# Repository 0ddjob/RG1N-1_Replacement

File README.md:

# RG1N-1_Replacement
Replacement board designs for the Soviet-era РГ1Н-1 connector

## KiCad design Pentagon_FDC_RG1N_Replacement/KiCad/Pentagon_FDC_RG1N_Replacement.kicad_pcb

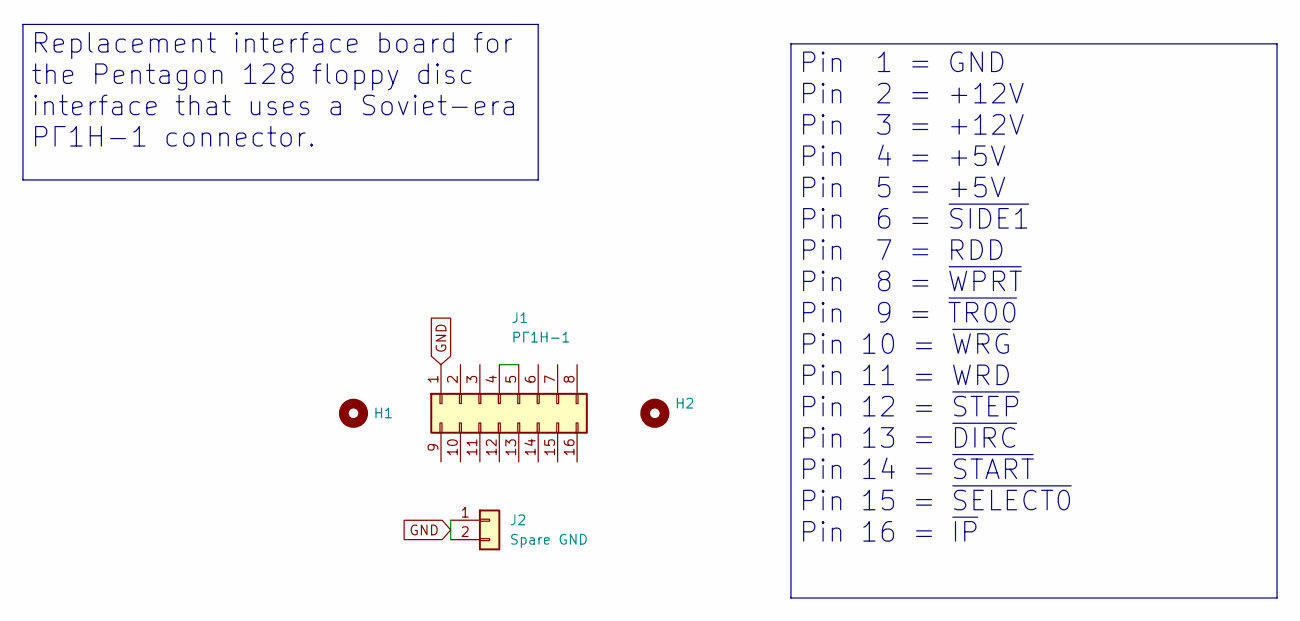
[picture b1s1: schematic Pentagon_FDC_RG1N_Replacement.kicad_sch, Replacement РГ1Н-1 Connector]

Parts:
H1, H2: MountingHole; MountingHole_3.2mm_M3
J1: РГ1Н-1; PinHeader_2x08_P2.54mm_Vertical
J2: Spare GND; PinHeader_1x02_P2.54mm_Vertical

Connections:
GND: J1.1, J2.1, J2.2
unnamed: J1.4, J1.5

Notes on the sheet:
Replacement interface board for the Pentagon 128 floppy disc interface that uses a Soviet-era РГ1Н-1 connector.
Pin 1 = GND Pin 2 = +12V Pin 3 = +12V Pin 4 = +5V Pin 5 = +5V Pin 6 = ~{SIDE1} Pin 7 = RDD Pin 8 = ~{WPRT} Pin 9 = ~{TR00} Pin 10 = ~{WRG} Pin 11 = WRD Pin 12 = ~{STEP} Pin 13 = ~{DIRC} Pin 14 = ~{START} Pin 15 = ~{SELECT0} Pin 16 = ~{IP}

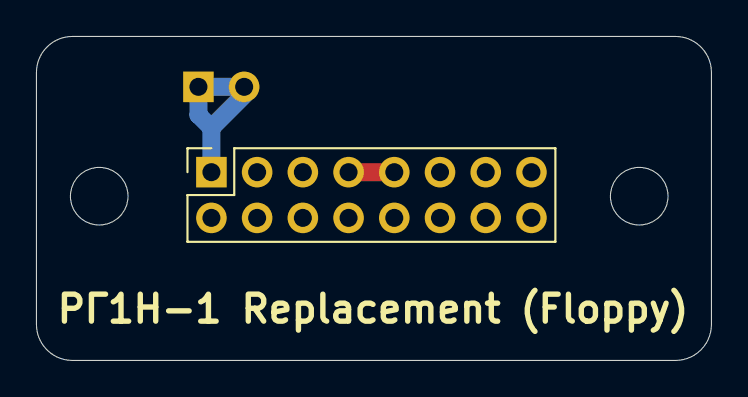
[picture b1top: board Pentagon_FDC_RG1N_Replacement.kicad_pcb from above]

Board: 2 copper layers, 37.5 x 18.0 mm, 4 parts (1 on the bottom side), 2 nets.

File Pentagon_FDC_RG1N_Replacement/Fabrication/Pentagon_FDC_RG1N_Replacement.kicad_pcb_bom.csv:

Designator,Quantity,Value,Footprint,Package,MPN,DNP,Mount_Type,Description
J1,1,РГ1Н-1,PinHeader_2x08_P2.54mm_Vertical,,,,tht,"Generic connector, double row, 02x08, top/bottom pin numbering scheme (row 1: 1...pins_per_row, row2: pins_per_row+1 ... num_pins), script generated (kicad-library-utils/schlib/autogen/connector/)"
J2,1,Spare GND,PinHeader_1x02_P2.54mm_Vertical,,,,tht,"Generic connector, single row, 01x02, script generated (kicad-library-utils/schlib/autogen/connector/)"
